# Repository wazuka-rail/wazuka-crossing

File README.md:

# Wazuka-Crossing
Miniature of a Japanese-style level crossing

## Full Version (with level crossing barriers)

**Under Development**

## Simple Version (without level crossing barriers)

### Schematic

### MCU
- PIC16F15213 PDIP / SOIC / DFN

|Pin| Name         | Function | Target    |
|---|--------------|----------|-----------|
| 1 | VDD          | VDD      |           |
| 2 | RA5          | DO       | Lamp 1    |
| 3 | RA4          | DO       | Lamp 2    |
| 4 | MCLR         | MCLR     |           |
| 5 | PWM3         | PWM      | Speaker 1 |
| 6 | ICSPCLK/PWM4 | ICSP/PWM | Speaker 2 |
| 7 | ICSPDAT      | ICSP/DI  | Button    |
| 8 | VSS          | VSS      |           |

## Timers
| Freq.  | Timer             | Purpose                           |
|-------:|:------------------|-----------------------------------|
| 20 kHz | Timer2            | Sound PWM (PWM3)                  |
| 156 Hz | Timer2 / 128      | Lamp PFM (S/W)                    |
| ~30 Hz | Timer2 / 4 / ~150 | Sound Modulation                  |
| 20 Hz  | Timer0            | Train Detection, Button           |
| 1.7 Hz | Timer0 / 12       | Lamp Flicker                      |

## Notes
The PICkit3 does not officially support the PIC16F152 family.
You can program PIC16F152 devices by PICkit3 with
[PICkitminus](http://kair.us/projects/pickitminus/).

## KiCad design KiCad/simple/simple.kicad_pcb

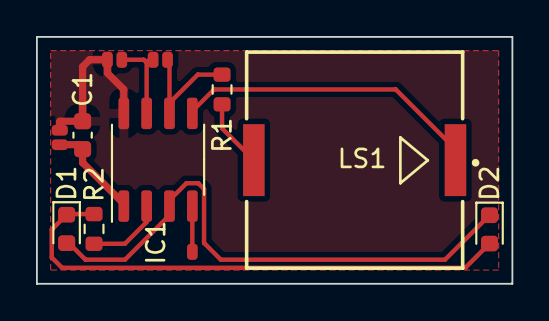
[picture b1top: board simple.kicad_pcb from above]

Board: 2 copper layers, 26.4 x 13.7 mm, 11 parts (0 on the bottom side), 10 nets.

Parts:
C1: 0.1u; C_0603_1608Metric
D1, D2: RED; LED_0603_1608Metric
IC1: PIC16F15213T-I_SN; SO-8_3.9x4.9mm_P1.27mm
J1, J2, J5: Conn_01x02; JP_2T
J3: Conn_01x01; JP_1T
LS1: PKLCS1212E2000-R1
R1: 1k; R_0603_1608Metric
R2: 100; R_0603_1608Metric

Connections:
+BATT: C1.1, IC1.1 (VDD), J1.1
/LAMP1: IC1.2 (RA5), R2.1
/LAMP2: D1.2 (A), D2.1 (K), IC1.3 (RA4)
/SPEAKER1: IC1.5 (RA2), LS1.1 (+)
GND: C1.2, IC1.8 (VSS), J1.2, J5.2
ICSPCLK: IC1.6 (RA1/ICSPCLK), J2.2, R1.2
ICSPDAT: IC1.7 (RA0/ICSPDAT), J2.1, J5.1
MCLR: IC1.4 (~MCLR/VPP/RA3), J3.1
unnamed: D1.1 (K), D2.2 (A), R2.2
unnamed: LS1.2 (-), R1.1

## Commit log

2023-07-31 Add the source codes of the simple version
2023-08-02 Add the KiCad project for the simple version
2023-08-02 Add the schematic image to README.md
2023-08-04 Add the title data of PCB
2023-08-17 Fix the footprint of C1
